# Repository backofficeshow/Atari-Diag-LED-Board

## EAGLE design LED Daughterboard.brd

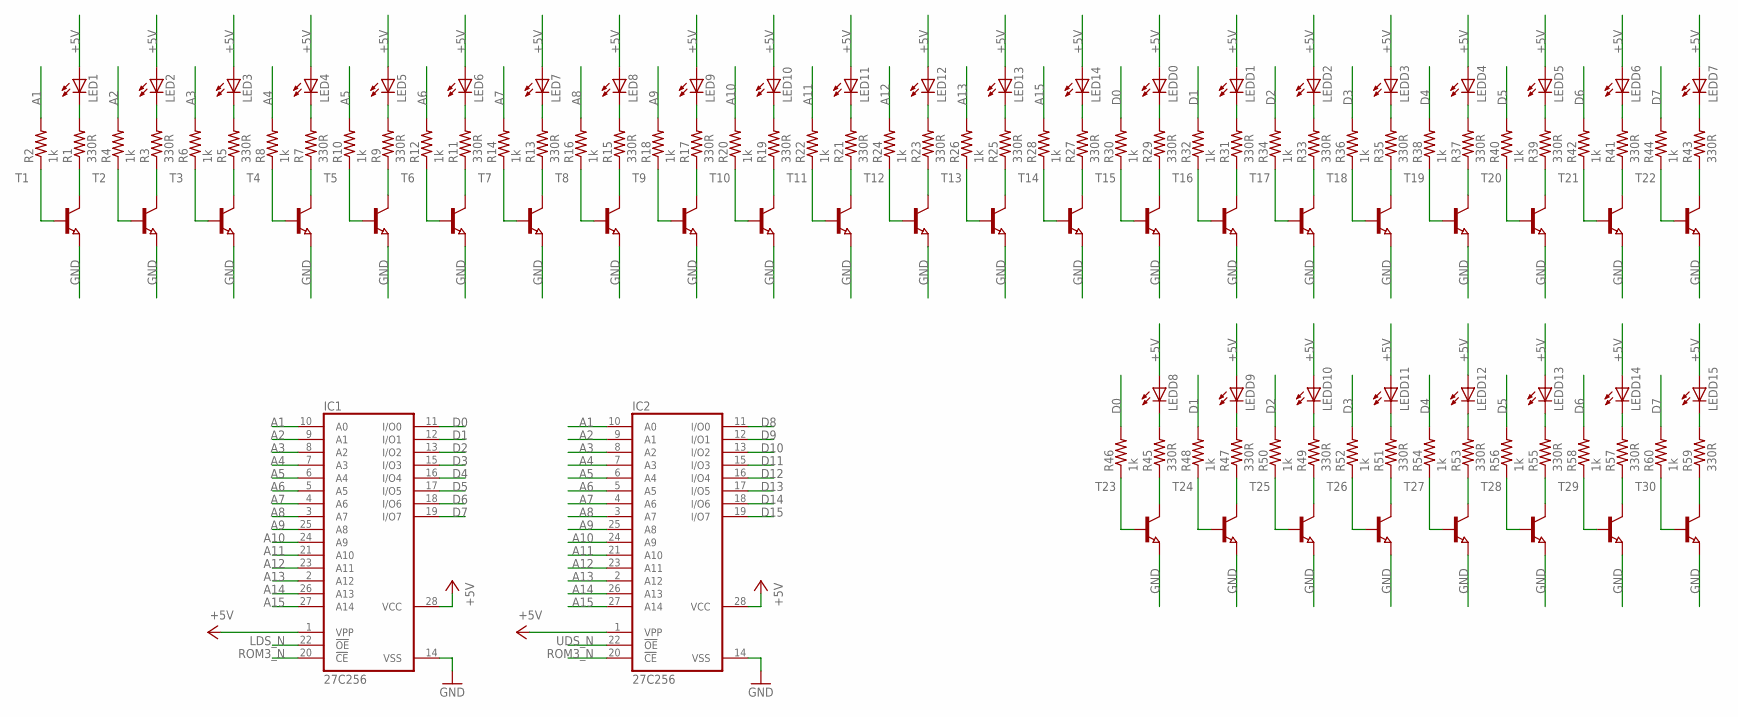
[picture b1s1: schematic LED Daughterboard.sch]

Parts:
IC1, IC2: 27C256; DIL28-6
LED1, LED2, LED3, LED4, LED5, LED6, LED7, LED8, LED9, LED10, LED11, LED12, LED13, LED14: LEDCHIP-LED0805; CHIP-LED0805
LEDD0, LEDD1, LEDD2, LEDD3, LEDD4, LEDD5, LEDD6, LEDD7, LEDD8, LEDD9, LEDD10, LEDD11, LEDD12, LEDD13, LEDD14, LEDD15: LEDCHIP-LED0805; CHIP-LED0805
R1, R3, R5, R7, R9, R11, R13, R15, R17, R19, R21, R23, R25, R27, R29, R31, R33, R35, R37, R39, R41, R43, R45, R47, R49, R51, R53, R55, R57, R59: 330R; M0805
R2, R4, R6, R8, R10, R12, R14, R16, R18, R20, R22, R24, R26, R28, R30, R32, R34, R36, R38, R40, R42, R44, R46, R48, R50, R52, R54, R56, R58, R60: 1k; M0805
T1, T2, T3, T4, T5, T6, T7, T8, T9, T10, T11, T12, T13, T14, T15, T16, T17, T18, T19, T20, T21, T22, T23, T24, T25, T26, T27, T28, T29, T30: NPN-TRANSISTOR_SOT23; SOT23

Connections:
+5V: IC1.1 (VPP), IC1.28 (VCC), IC2.1 (VPP), IC2.28 (VCC), LED1.A, LED2.A, LED3.A, LED4.A, LED5.A, LED6.A, LED7.A, LED8.A, LED9.A, LED10.A, LED11.A, LED12.A, LED13.A, LED14.A, LEDD0.A, LEDD1.A, LEDD2.A, LEDD3.A, LEDD4.A, LEDD5.A, LEDD6.A, LEDD7.A, LEDD8.A, LEDD9.A, LEDD10.A, LEDD11.A, LEDD12.A, LEDD13.A, LEDD14.A, LEDD15.A
A1: IC1.10 (A0), IC2.10 (A0), R2.2
A2: IC1.9 (A1), IC2.9 (A1), R4.2
A3: IC1.8 (A2), IC2.8 (A2), R6.2
A4: IC1.7 (A3), IC2.7 (A3), R8.2
A5: IC1.6 (A4), IC2.6 (A4), R10.2
A6: IC1.5 (A5), IC2.5 (A5), R12.2
A7: IC1.4 (A6), IC2.4 (A6), R14.2
A8: IC1.3 (A7), IC2.3 (A7), R16.2
A9: IC1.25 (A8), IC2.25 (A8), R18.2
A10: IC1.24 (A9), IC2.24 (A9), R20.2
A11: IC1.21 (A10), IC2.21 (A10), R22.2
A12: IC1.23 (A11), IC2.23 (A11), R24.2
A13: IC1.2 (A12), IC2.2 (A12), R26.2
A14: IC1.26 (A13), IC2.26 (A13)
A15: IC1.27 (A14), IC2.27 (A14), R28.2
D0: IC1.11 (I/O0), R30.2, R46.2
D1: IC1.12 (I/O1), R32.2, R48.2
D2: IC1.13 (I/O2), R34.2, R50.2
D3: IC1.15 (I/O3), R36.2, R52.2
D4: IC1.16 (I/O4), R38.2, R54.2
D5: IC1.17 (I/O5), R40.2, R56.2
D6: IC1.18 (I/O6), R42.2, R58.2
D7: IC1.19 (I/O7), R44.2, R60.2
D8: IC2.11 (I/O0)
D9: IC2.12 (I/O1)
D10: IC2.13 (I/O2)
D11: IC2.15 (I/O3)
D12: IC2.16 (I/O4)
D13: IC2.17 (I/O5)
D14: IC2.18 (I/O6)
D15: IC2.19 (I/O7)
GND: IC1.14 (VSS), IC2.14 (VSS), T1.2 (E), T2.2 (E), T3.2 (E), T4.2 (E), T5.2 (E), T6.2 (E), T7.2 (E), T8.2 (E), T9.2 (E), T10.2 (E), T11.2 (E), T12.2 (E), T13.2 (E), T14.2 (E), T15.2 (E), T16.2 (E), T17.2 (E), T18.2 (E), T19.2 (E), T20.2 (E), T21.2 (E), T22.2 (E), T23.2 (E), T24.2 (E), T25.2 (E), T26.2 (E), T27.2 (E), T28.2 (E), T29.2 (E), T30.2 (E)
LDS_N: IC1.22 (!OE)
unnamed: R2.1, T1.1 (B)
unnamed: LED1.C, R1.2
unnamed: R1.1, T1.3 (C)
unnamed: LEDD4.C, R37.2
unnamed: LED2.C, R3.2
unnamed: R3.1, T2.3 (C)
unnamed: R4.1, T2.1 (B)
unnamed: LED3.C, R5.2
unnamed: R5.1, T3.3 (C)
unnamed: R6.1, T3.1 (B)
unnamed: LED4.C, R7.2
unnamed: R7.1, T4.3 (C)
unnamed: R8.1, T4.1 (B)
unnamed: LED5.C, R9.2
unnamed: R9.1, T5.3 (C)
unnamed: R10.1, T5.1 (B)
unnamed: LED6.C, R11.2
unnamed: R11.1, T6.3 (C)
unnamed: R12.1, T6.1 (B)
unnamed: LED7.C, R13.2
unnamed: R13.1, T7.3 (C)
unnamed: R14.1, T7.1 (B)
unnamed: LED8.C, R15.2
unnamed: R15.1, T8.3 (C)
unnamed: R16.1, T8.1 (B)
unnamed: LED9.C, R17.2
unnamed: R17.1, T9.3 (C)
unnamed: R18.1, T9.1 (B)
unnamed: LED10.C, R19.2
unnamed: R19.1, T10.3 (C)
unnamed: R20.1, T10.1 (B)
unnamed: LED11.C, R21.2
unnamed: R21.1, T11.3 (C)
unnamed: R22.1, T11.1 (B)
unnamed: LED12.C, R23.2
unnamed: R23.1, T12.3 (C)
unnamed: R24.1, T12.1 (B)
unnamed: LED13.C, R25.2
unnamed: R25.1, T13.3 (C)
unnamed: R26.1, T13.1 (B)
unnamed: LED14.C, R27.2
unnamed: R27.1, T14.3 (C)
unnamed: R28.1, T14.1 (B)
unnamed: LEDD0.C, R29.2
unnamed: R29.1, T15.3 (C)
unnamed: R30.1, T15.1 (B)
unnamed: LEDD1.C, R31.2
unnamed: R31.1, T16.3 (C)
unnamed: R32.1, T16.1 (B)
unnamed: LEDD2.C, R33.2
unnamed: R33.1, T17.3 (C)
unnamed: R34.1, T17.1 (B)
unnamed: LEDD3.C, R35.2
unnamed: R35.1, T18.3 (C)
unnamed: R36.1, T18.1 (B)
unnamed: R37.1, T19.3 (C)
unnamed: R38.1, T19.1 (B)
unnamed: LEDD5.C, R39.2
unnamed: R39.1, T20.3 (C)
unnamed: R40.1, T20.1 (B)
unnamed: LEDD6.C, R41.2
unnamed: R41.1, T21.3 (C)
unnamed: R42.1, T21.1 (B)
unnamed: LEDD7.C, R43.2
unnamed: R43.1, T22.3 (C)
unnamed: R44.1, T22.1 (B)
unnamed: LEDD8.C, R45.2
unnamed: R45.1, T23.3 (C)
unnamed: R46.1, T23.1 (B)
unnamed: LEDD9.C, R47.2
unnamed: R47.1, T24.3 (C)
unnamed: R48.1, T24.1 (B)
unnamed: LEDD10.C, R49.2
unnamed: R49.1, T25.3 (C)
unnamed: R50.1, T25.1 (B)
unnamed: LEDD11.C, R51.2
unnamed: R51.1, T26.3 (C)
unnamed: R52.1, T26.1 (B)
unnamed: LEDD12.C, R53.2
unnamed: R53.1, T27.3 (C)
unnamed: R54.1, T27.1 (B)
unnamed: LEDD13.C, R55.2
unnamed: R55.1, T28.3 (C)
unnamed: R56.1, T28.1 (B)
unnamed: LEDD14.C, R57.2
unnamed: R57.1, T29.3 (C)
unnamed: R58.1, T29.1 (B)
unnamed: LEDD15.C, R59.2
unnamed: R59.1, T30.3 (C)
unnamed: R60.1, T30.1 (B)
ROM3_N: IC1.20 (!CE), IC2.20 (!CE)
UDS_N: IC2.22 (!OE)

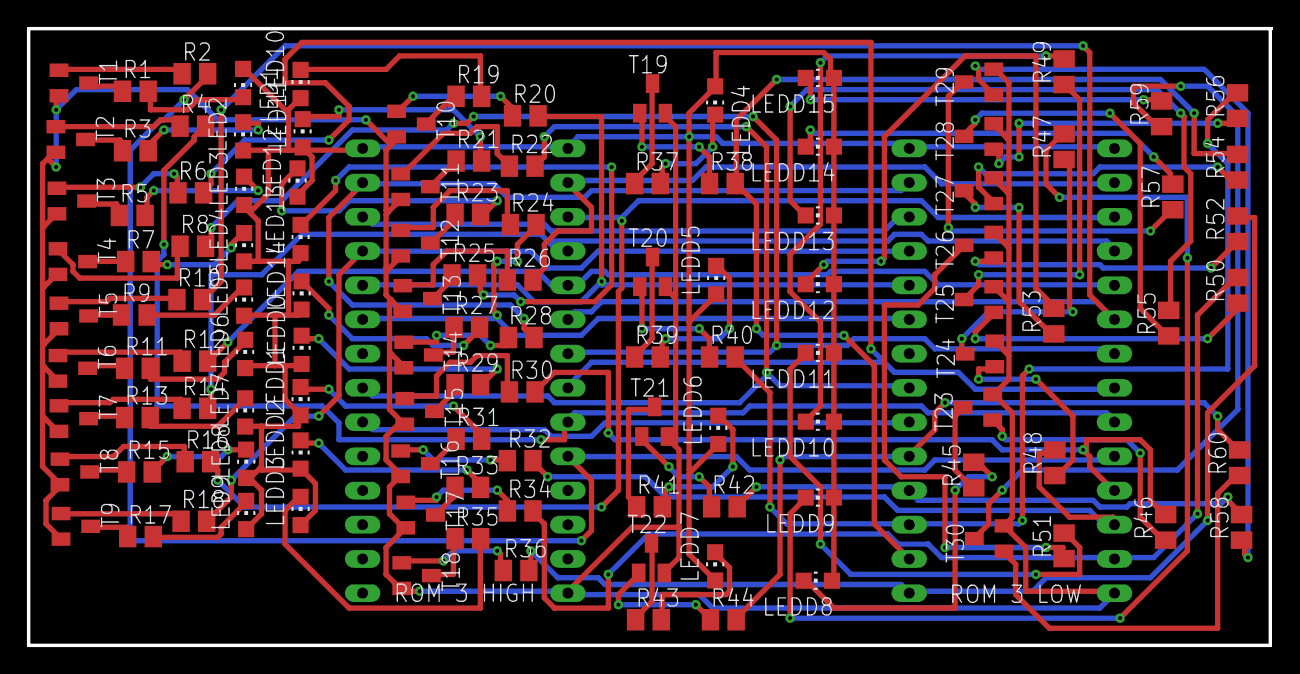
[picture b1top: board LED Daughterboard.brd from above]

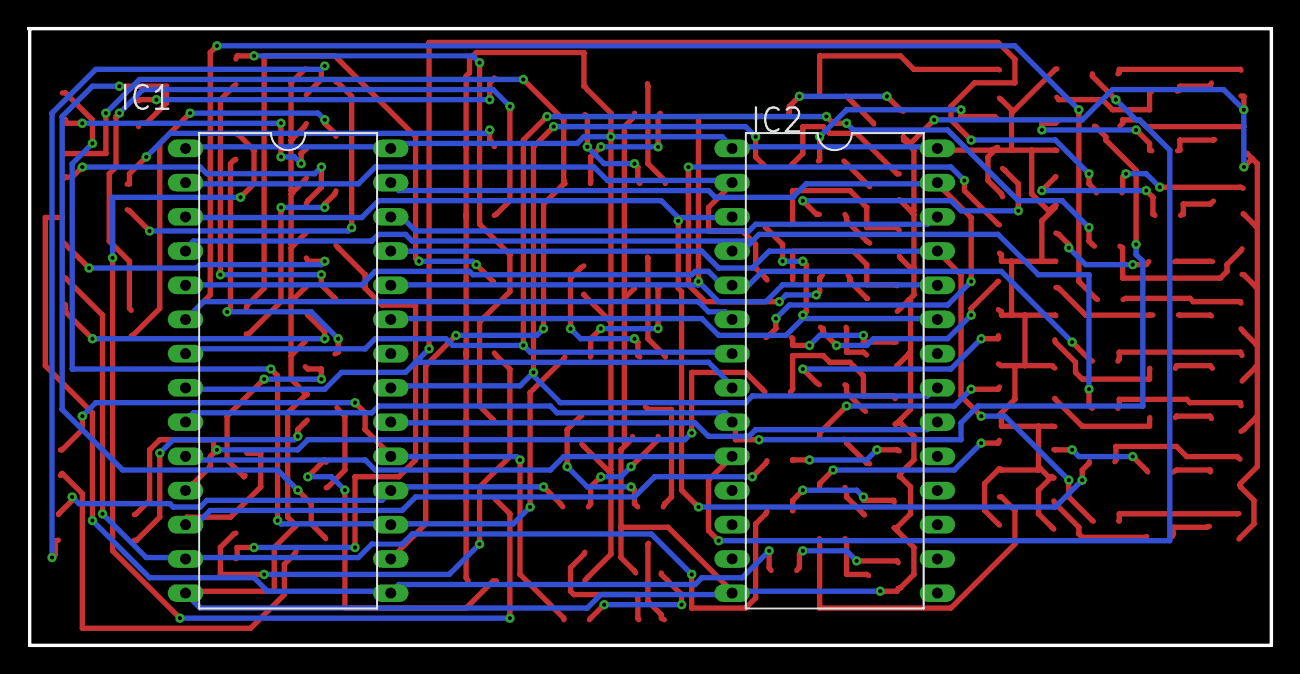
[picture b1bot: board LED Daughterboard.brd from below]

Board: 2 copper layers, 92.3 x 45.8 mm, 122 parts (2 on the bottom side), 116 nets.

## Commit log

2019-10-08 No one is ever going to build this
    However, the best design (competition to end when I decide) will win a Diag card PCB.
